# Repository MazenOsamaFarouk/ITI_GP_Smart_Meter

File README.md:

# ITI_GP_Smart_Meter
 Final Project for ITI program. ITs an IOT energy meter using Raspberry Pi and ARM

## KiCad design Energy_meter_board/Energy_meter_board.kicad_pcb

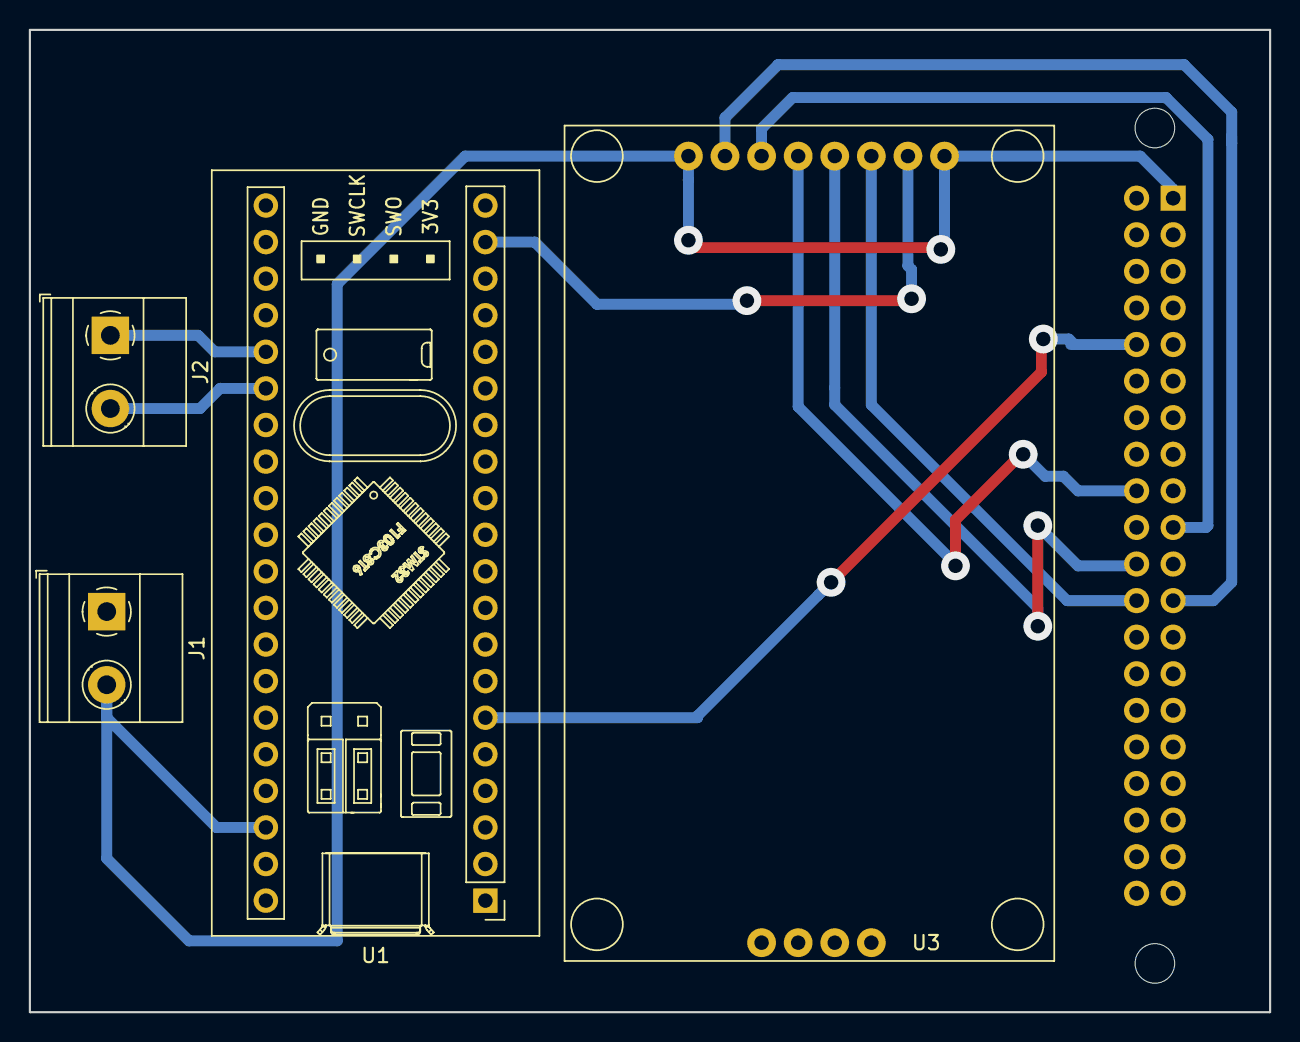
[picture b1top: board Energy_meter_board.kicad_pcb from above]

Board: 2 copper layers, 86.1 x 68.2 mm, 5 parts (1 on the bottom side), 10 nets.

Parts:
J1, J2: Screw_Terminal_01x02; TerminalBlock_Phoenix_MKDS-1,5-2-5.08_1x02_P5.08mm_Horizont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
RP1: Raspberry_Pi_2_3; raspberrypi2
U1: YAAJ_BluePill; YAAJ_BluePill_1
U3: TFT_ST7735_symbol; ST7735_TFT_DISP

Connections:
+3V3: J1.2, RP1.1, U1.38, U3.1, U3.8
CURRENT_SENSOR: J2.2, U1.26
DISP_A0: RP1.18, U3.5
DISP_CS: RP1.24, U3.3
DISP_RST: RP1.22, U3.4
DISP_SCK: RP1.23, U3.7
DISP_SDA: RP1.19, U3.6
GNDREF: J1.1, RP1.25, U1.19, U3.2
RPi_UART_RX: RP1.10, U1.6
VOLTAGE_SENSOR: J2.1, U1.25

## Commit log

2021-02-20 started the repo and added the meter python source code
2021-02-20 - integrated display code with google Sheets Code - created modules for ease of use for bith display and sheets
2021-02-20 created modules for google sheets and display
2021-03-08 added STM32 Project
2021-03-09 added UART test python script
2021-03-09 implemented a uart interface with pySerial module
2021-03-09 added a log file for capturing errors, mainly created by the UART module
2021-03-09 a test file to test threading with times and uart at the same time before integration
2021-03-09 renamed UART_test to UART_Interface
2021-03-09 other minor changes
2021-03-12 in main.c : changed calculation methods of Power , Current and Voltage and Added calculation of Real Power
2021-03-13 added some clarification comments on the ISR callback calculations
2021-03-13 orgainzed code into threads and added power and energy calculations
2021-03-19 added PCB files to the repo
